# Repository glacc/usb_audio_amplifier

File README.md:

# USB_Audio_Amplifier

设计属于自己的DSP收音机的过程中开启的分支xwx

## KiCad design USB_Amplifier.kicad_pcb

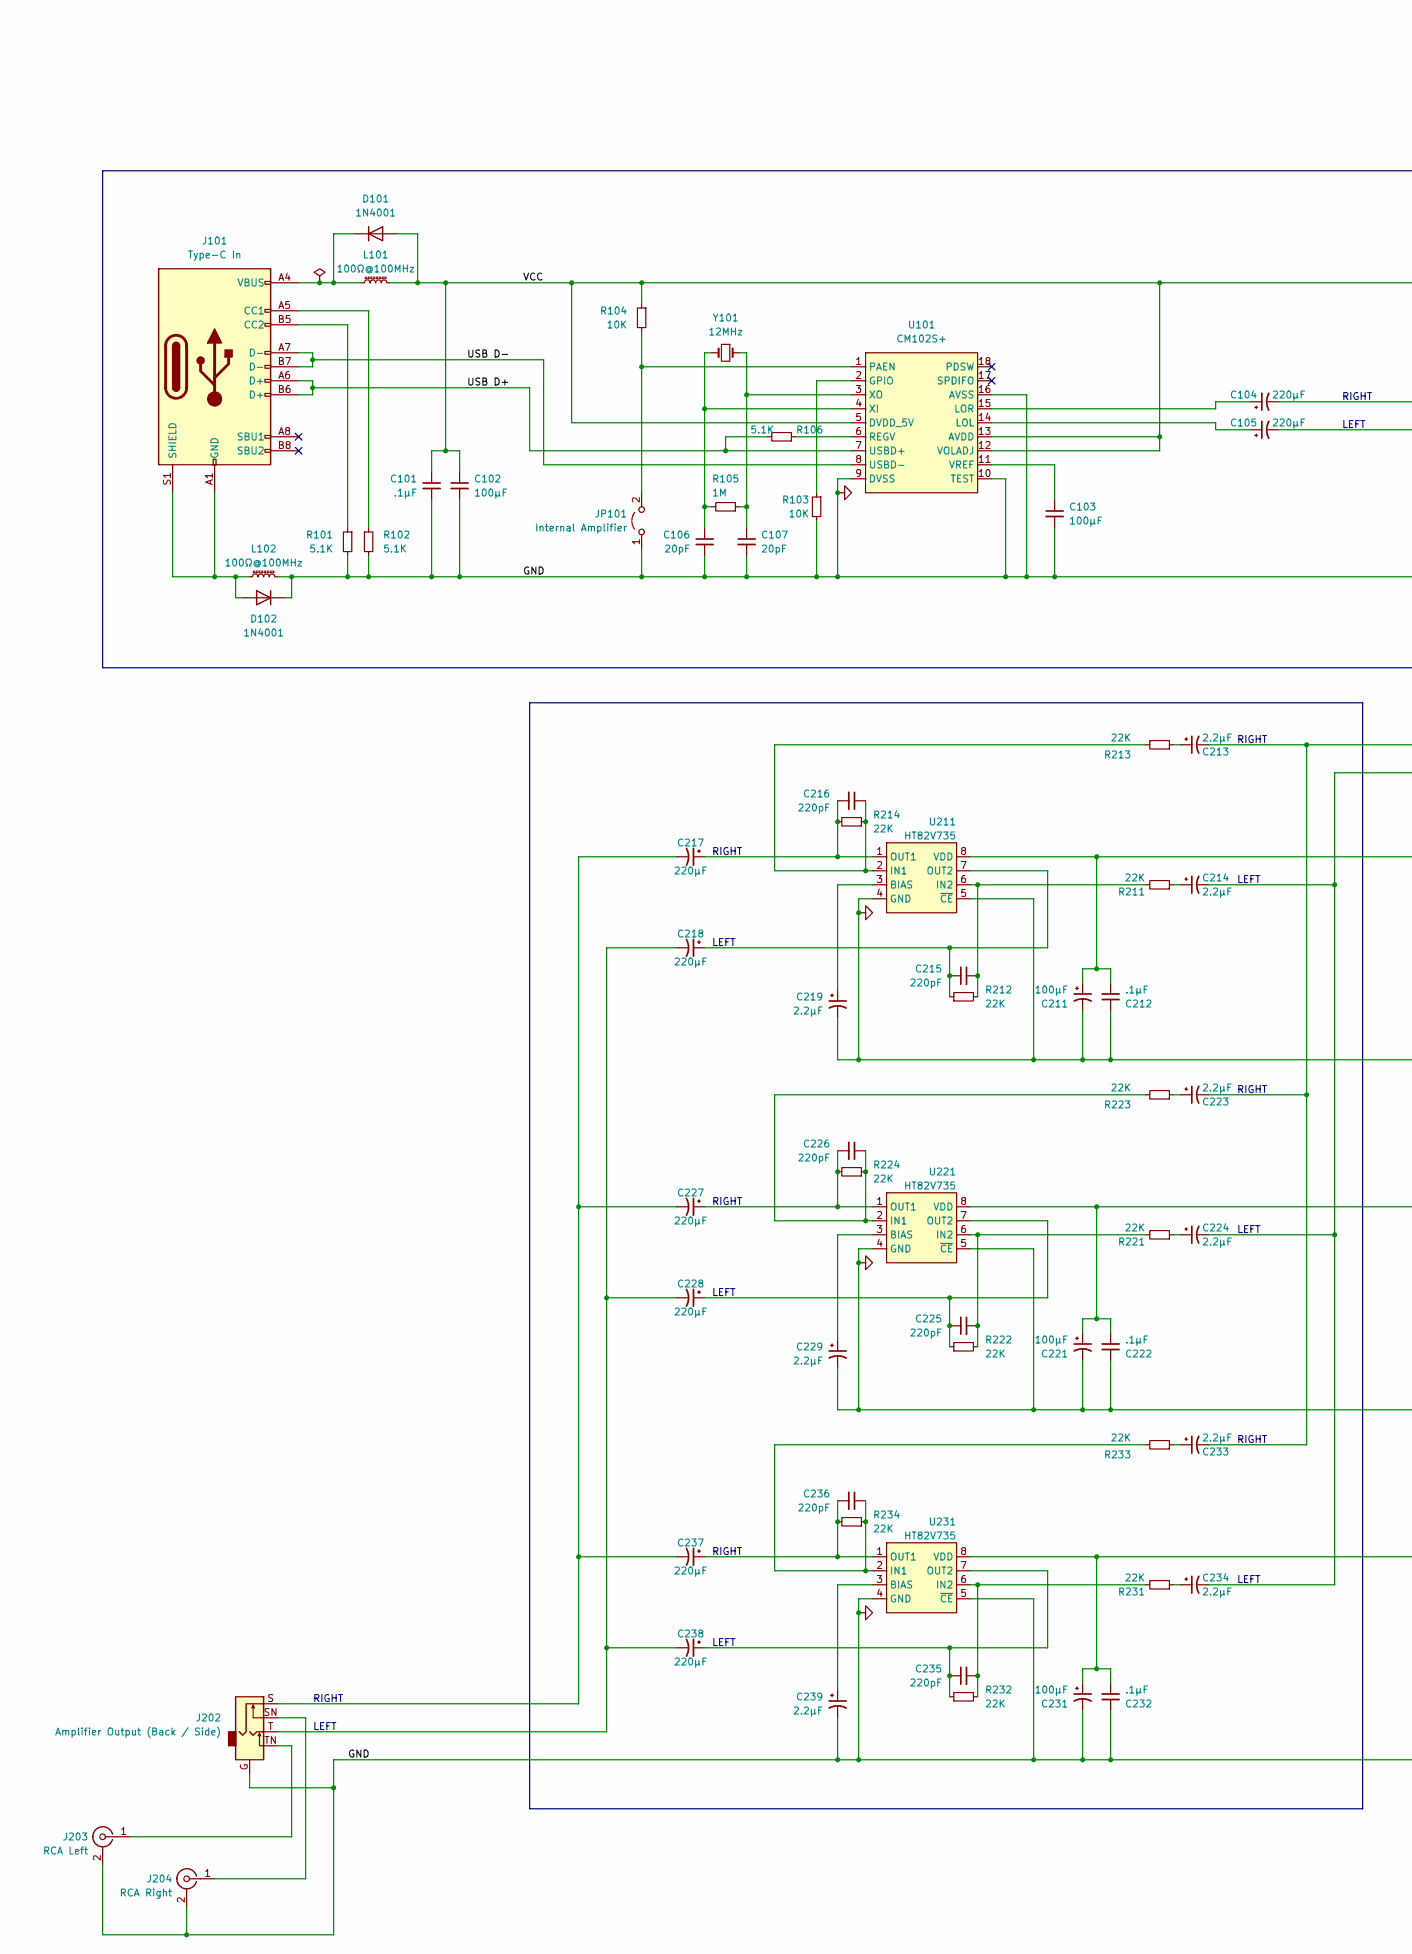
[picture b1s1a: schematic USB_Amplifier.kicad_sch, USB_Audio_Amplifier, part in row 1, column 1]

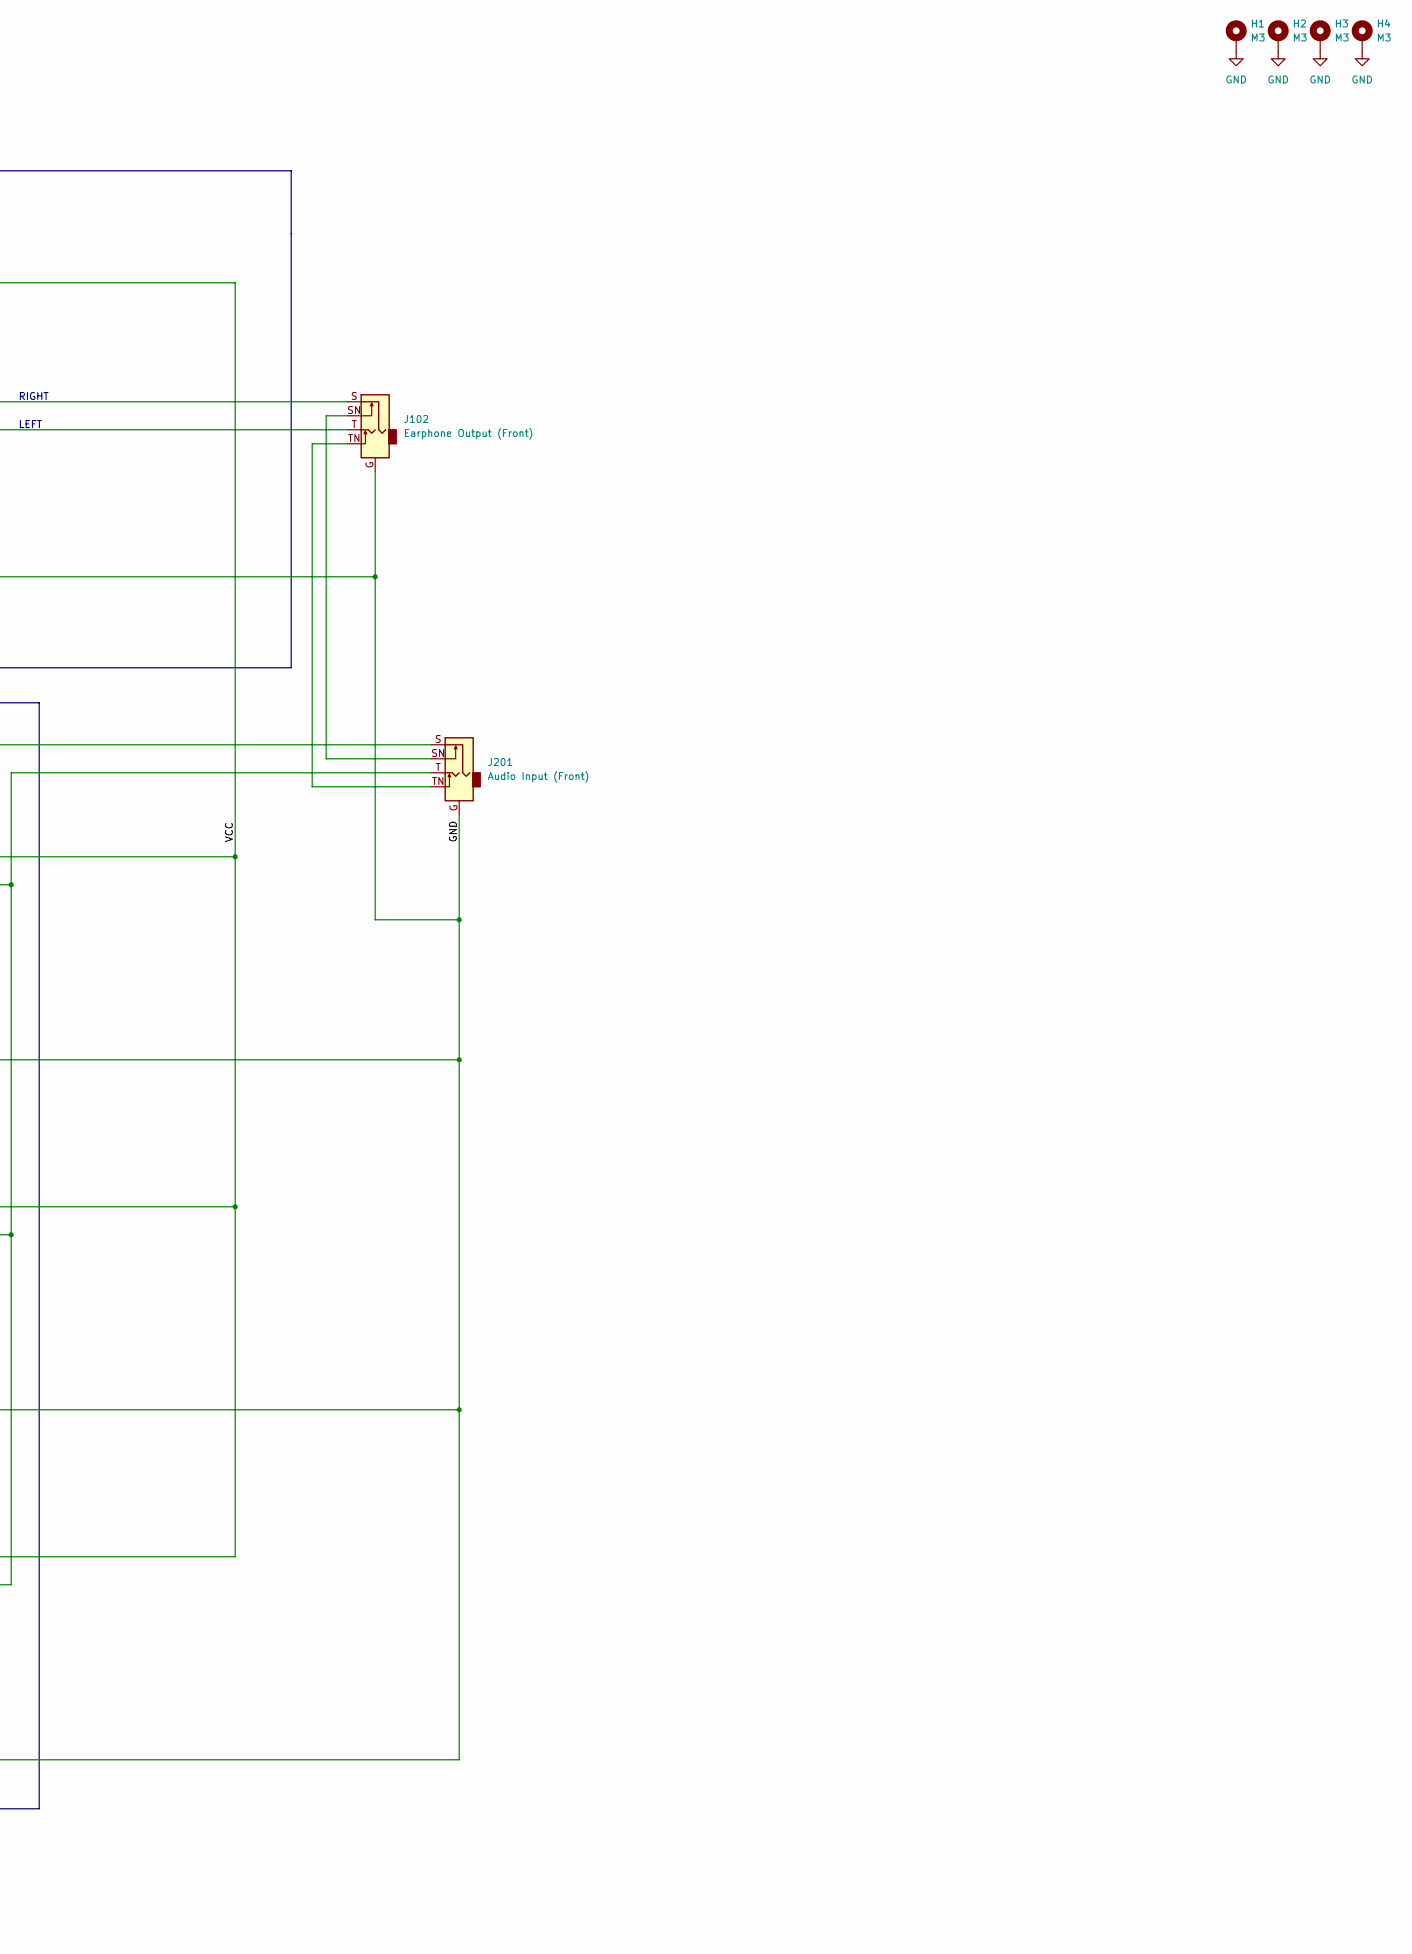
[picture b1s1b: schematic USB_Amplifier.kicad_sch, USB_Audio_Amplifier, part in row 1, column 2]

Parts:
C101, C212, C222, C232: .1μF; C_0603_1608Metric_Pad1.08x0.95mm_HandSolder
C102, C103, C211, C221, C231: 100μF; CP_Radial_D6.3mm_P2.50mm
C104, C105, C217, C218, C227, C228, C237, C238: 220μF; CP_Radial_D8.0mm_P3.50mm
C106, C107: 20pF; C_0603_1608Metric_Pad1.08x0.95mm_HandSolder
C213, C214, C219, C223, C224, C229, C233, C234, C239: 2.2μF; C_1206_3216Metric_Pad1.33x1.80mm_HandSolder
C215, C216, C225, C226, C235, C236: 220pF; C_0603_1608Metric_Pad1.08x0.95mm_HandSolder
D101, D102: 1N4001; D_SMA_Handsoldering
H1, H2, H3, H4: M3; MountingHole_3.2mm_M3_DIN965_Pad
J101: Type-C In; USB_C_Receptacle_HRO_TYPE-C-31-M-12
J102: Earphone Output (Front); Jack_3.5mm
J201: Audio Input (Front); Jack_3.5mm
J202: Amplifier Output (Back / Side); Jack_3.5mm
J203: RCA Left; RCA_1
J204: RCA Right; RCA_1
JP101: Internal Amplifier; PinHeader_1x02_P2.54mm_Vertical
L101, L102: 100Ω@100MHz; L_1206_3216Metric_Pad1.42x1.75mm_HandSolder
R101, R102, R106: 5.1K; R_1206_3216Metric_Pad1.30x1.75mm_HandSolder
R103, R104: 10K; R_0603_1608Metric_Pad0.98x0.95mm_HandSolder
R105: 1M; R_0805_2012Metric_Pad1.20x1.40mm_HandSolder
R211, R212, R213, R214, R221, R222, R223, R224, R231, R232, R233, R234: 22K; R_1206_3216Metric_Pad1.30x1.75mm_HandSolder
U101: CM102S+; SOP-18_7x12.5mm_P1.27mm
U211, U221, U231: HT82V735; SOP-8_3.76x4.96mm_P1.27mm
Y101: 12MHz; Crystal_HC49-U_Vertical

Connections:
/USB D+: J101.A6 (D+), J101.B6 (D+), R106.2, U101.7 (USBD+)
/USB D-: J101.A7 (D-), J101.B7 (D-), U101.8 (USBD-)
/VCC: C101.1, C102.1, C211.1, C212.2, C221.1, C222.2, C231.1, C232.2, D101.2 (A), L101.2, R104.1, U101.5 (DVDD_5V), U101.12 (VOLADJ), U101.13 (AVDD), U211.8 (VDD), U221.8 (VDD), U231.8 (VDD)
GND: C101.2, C102.2, C103.2, C106.2, C107.2, C211.2, C212.1, C219.2, C221.2, C222.1, C229.2, C231.2, C232.1, C239.2, D102.1 (K), H1.1, H2.1, H3.1, H4.1, J102.G, J201.G, J202.G, J203.2 (Ext), J204.2 (Ext), JP101.1 (A), L102.2, R101.2, R102.2, R103.2, U101.9 (DVSS), U101.10 (TEST), U101.16 (AVSS), U211.4 (GND), U211.5 (~CE), U221.4 (GND), U221.5 (~CE), U231.4 (GND), U231.5 (~CE)
unnamed: C103.1, U101.11 (VREF)
unnamed: C104.1, U101.15 (LOR)
unnamed: C104.2, J102.S
unnamed: C105.1, U101.14 (LOL)
unnamed: C105.2, J102.T
unnamed: C106.1, R105.2, U101.4 (XI), Y101.2
unnamed: C107.1, R105.1, U101.3 (XO), Y101.1
unnamed: C213.1, R213.1
unnamed: C213.2, C223.2, C233.2, J201.S
unnamed: C214.1, R211.1
unnamed: C214.2, C224.2, C234.2, J201.T
unnamed: C215.1, C218.1, R212.1, U211.7 (OUT2)
unnamed: C215.2, R211.2, R212.2, U211.6 (IN2)
unnamed: C216.1, R213.2, R214.1, U211.2 (IN1)
unnamed: C216.2, C217.1, R214.2, U211.1 (OUT1)
unnamed: C217.2, C227.2, C237.2, J202.S
unnamed: C218.2, C228.2, C238.2, J202.T
unnamed: C219.1, U211.3 (BIAS)
unnamed: C223.1, R223.1
unnamed: C224.1, R221.1
unnamed: C225.1, C228.1, R222.1, U221.7 (OUT2)
unnamed: C225.2, R221.2, R222.2, U221.6 (IN2)
unnamed: C226.1, R223.2, R224.1, U221.2 (IN1)
unnamed: C226.2, C227.1, R224.2, U221.1 (OUT1)
unnamed: C229.1, U221.3 (BIAS)
unnamed: C233.1, R233.1
unnamed: C234.1, R231.1
unnamed: C235.1, C238.1, R232.1, U231.7 (OUT2)
unnamed: C235.2, R231.2, R232.2, U231.6 (IN2)
unnamed: C236.1, R233.2, R234.1, U231.2 (IN1)
unnamed: C236.2, C237.1, R234.2, U231.1 (OUT1)
unnamed: C239.1, U231.3 (BIAS)
unnamed: D101.1 (K), J101.A4 (VBUS), J101.A9 (VBUS), J101.B4 (VBUS), J101.B9 (VBUS), L101.1
unnamed: D102.2 (A), J101.A1 (GND), J101.A12 (GND), J101.B1 (GND), J101.B12 (GND), J101.S1 (SHIELD), L102.1
unnamed: J101.A5 (CC1), R102.1
unnamed: J101.B5 (CC2), R101.1
unnamed: J102.SN, J201.SN
unnamed: J102.TN, J201.TN
unnamed: J202.SN, J204.1 (In)
unnamed: J202.TN, J203.1 (In)
unnamed: JP101.2 (B), R104.2, U101.1 (PAEN)
unnamed: R103.1, U101.2 (GPIO)
unnamed: R106.1, U101.6 (REGV)

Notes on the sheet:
RIGHT
LEFT

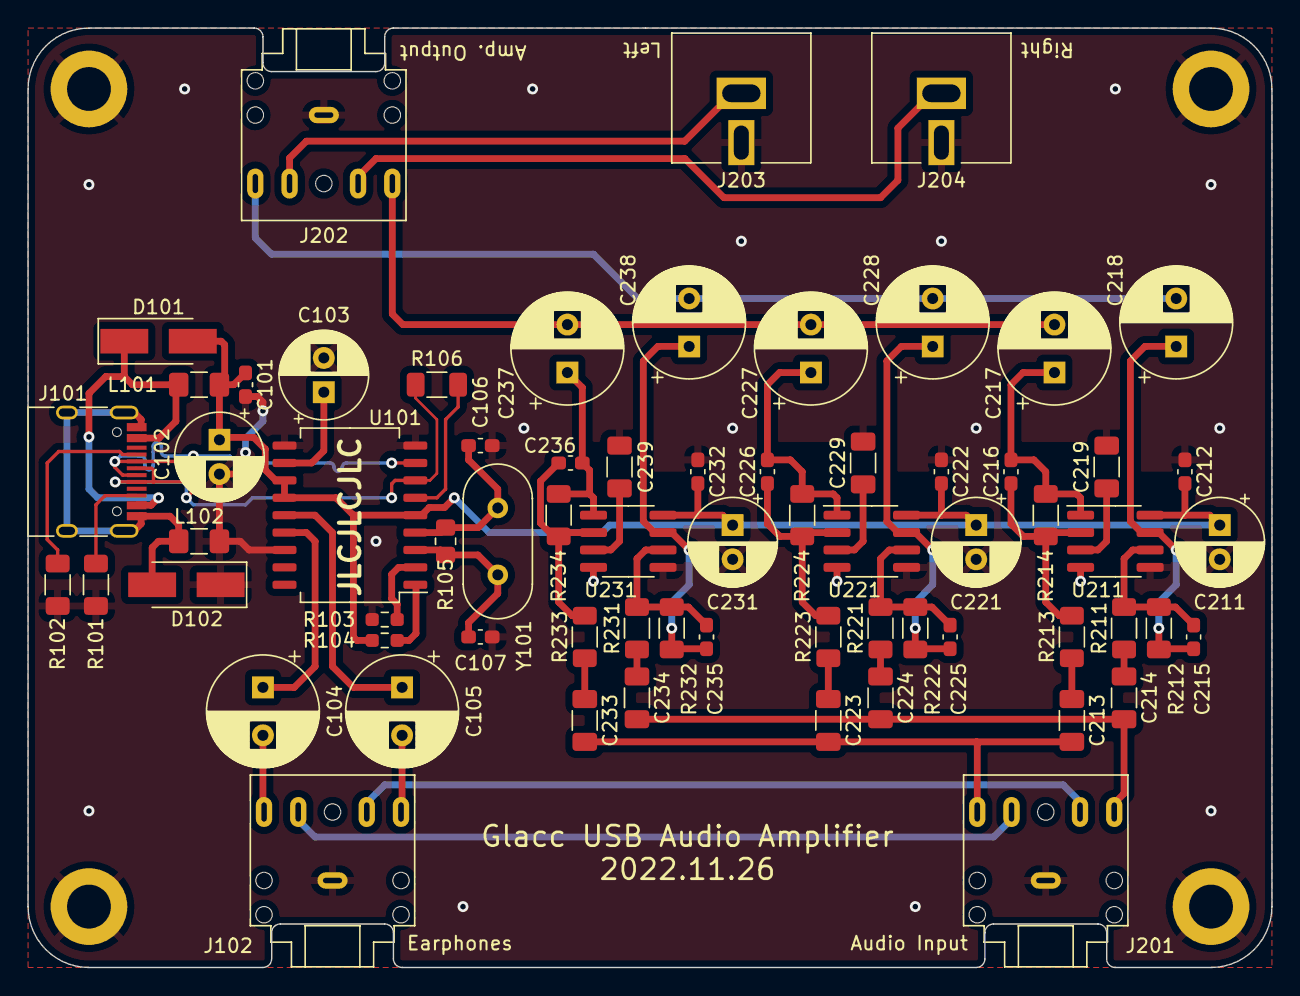
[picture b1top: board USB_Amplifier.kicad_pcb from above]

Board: 2 copper layers, 90.8 x 68.6 mm, 71 parts (0 on the bottom side), 47 nets.

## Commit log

2022-12-06 Create LICENCE
